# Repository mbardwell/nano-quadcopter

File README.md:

# Nano Quadcopter Project

## Overview

Welcome to the Nano Quadcopter project! This repository contains all the necessary files and instructions to build and program your own nano quadcopter.

The repository is in such a state that it would be better used as source code than an instruction manual.

This project is heavily inspired by Carbon Aeronautic's drone series [YT](https://www.youtube.com/@carbonaeronautics).

## Features

- Compact and lightweight design
- Easy to assemble
- Customizable firmware
- Open-source hardware and software

## Getting Started

### Prerequisites

- KiCad installed
- Arduino installed
- Electronics and soldering equipment

## License

This project is licensed under a standard MIT License.

## Contact

For any questions or feedback, please open an issue or contact us at [github.com.casually782@passinbox.com](mailto:github.com.casually782@passinbox.com).

Happy flying!

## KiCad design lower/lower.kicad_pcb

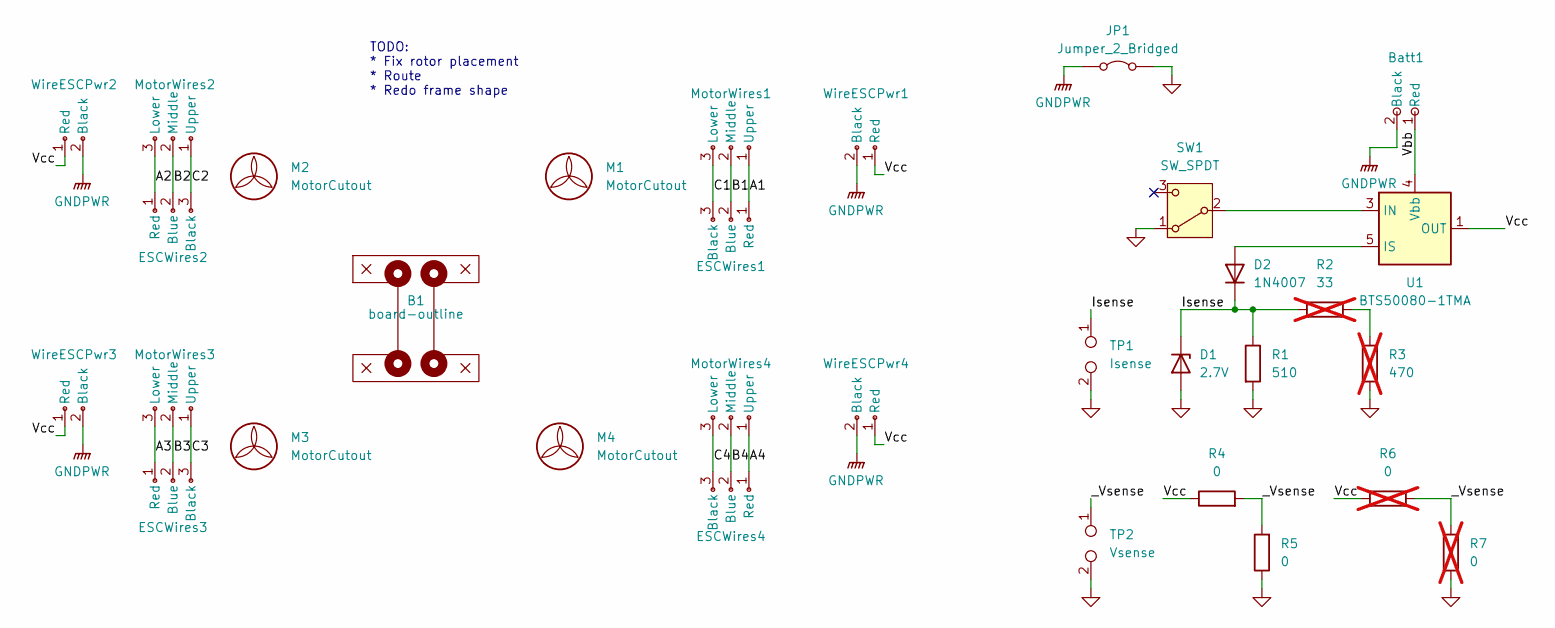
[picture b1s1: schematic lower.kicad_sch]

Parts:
B1: board-outline; board-outline-test
Batt1: WireBatt
D1: 2.7V; D_T-1_P5.08mm_Horizontal
D2: 1N4007; D_DO-41_SOD81_P10.16mm_Horizontal
ESCWires1, ESCWires2, ESCWires3, ESCWires4: WireESC
H1, H2, H3, H4: MountingHole; MountingHole_3.2mm_M3_ISO14580
JP1: Jumper_2_Bridged; SolderJumperLarge
M1, M2, M3, M4: MotorCutout; MotorEdges
MotorWires1, MotorWires2, MotorWires3, MotorWires4: WireMotor
R1: 510; R_0201_0603Metric_Pad0.64x0.40mm_HandSolder
R2: 33; R_Axial_DIN0207_L6.3mm_D2.5mm_P7.62mm_Horizontal; not fitted
R3: 470; R_Axial_DIN0207_L6.3mm_D2.5mm_P7.62mm_Horizontal; not fitted
R4, R5: 0; R_1206_3216Metric_Pad1.30x1.75mm_HandSolder
R6, R7: 0; R_Axial_DIN0207_L6.3mm_D2.5mm_P7.62mm_Horizontal; not fitted
SW1: SW_SPDT; SW_Slide_SPDT_Angled_CK_OS102011MA1Q
TP1: Isense; TestPoint_2Pads_Pitch2.54mm_Drill0.8mm
TP2: Vsense; TestPoint_2Pads_Pitch2.54mm_Drill0.8mm
U1: BTS50080-1TMA; TO-263-7_TabPin4
WireESCPwr1, WireESCPwr2, WireESCPwr3, WireESCPwr4: WireESCPwr

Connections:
/A1: ESCWires1.1 (Red), MotorWires1.1 (Upper)
/A2: ESCWires2.1 (Red), MotorWires2.3 (Lower)
/A3: ESCWires3.1 (Red), MotorWires3.3 (Lower)
/A4: ESCWires4.1 (Red), MotorWires4.1 (Upper)
/B1: ESCWires1.2 (Blue), MotorWires1.2 (Middle)
/B2: ESCWires2.2 (Blue), MotorWires2.2 (Middle)
/B3: ESCWires3.2 (Blue), MotorWires3.2 (Middle)
/B4: ESCWires4.2 (Blue), MotorWires4.2 (Middle)
/C1: ESCWires1.3 (Black), MotorWires1.3 (Lower)
/C2: ESCWires2.3 (Black), MotorWires2.1 (Upper)
/C3: ESCWires3.3 (Black), MotorWires3.1 (Upper)
/C4: ESCWires4.3 (Black), MotorWires4.3 (Lower)
/Isense: D1.1 (K), D2.1 (K), R1.1, R2.1, TP1.1
/Vbb: Batt1.1 (Red), U1.4 (Vbb)
/Vcc: R4.1, R6.1, U1.1 (OUT), U1.2 (OUT), U1.6 (OUT), U1.7 (OUT), WireESCPwr1.1 (Red), WireESCPwr2.1 (Red), WireESCPwr3.1 (Red), WireESCPwr4.1 (Red)
/_Vsense: R4.2, R5.2, R6.2, R7.1, TP2.1
GND: D1.2 (A), JP1.2 (B), R1.2, R3.2, R5.1, R7.2, SW1.1 (A), TP1.2, TP2.2
GNDPWR: Batt1.2 (Black), JP1.1 (A), WireESCPwr1.2 (Black), WireESCPwr2.2 (Black), WireESCPwr3.2 (Black), WireESCPwr4.2 (Black)
unnamed: D2.2 (A), U1.5 (IS)
unnamed: R2.2, R3.1
unnamed: SW1.2 (B), U1.3 (IN)

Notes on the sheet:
TODO: * Fix rotor placement * Route * Redo frame shape

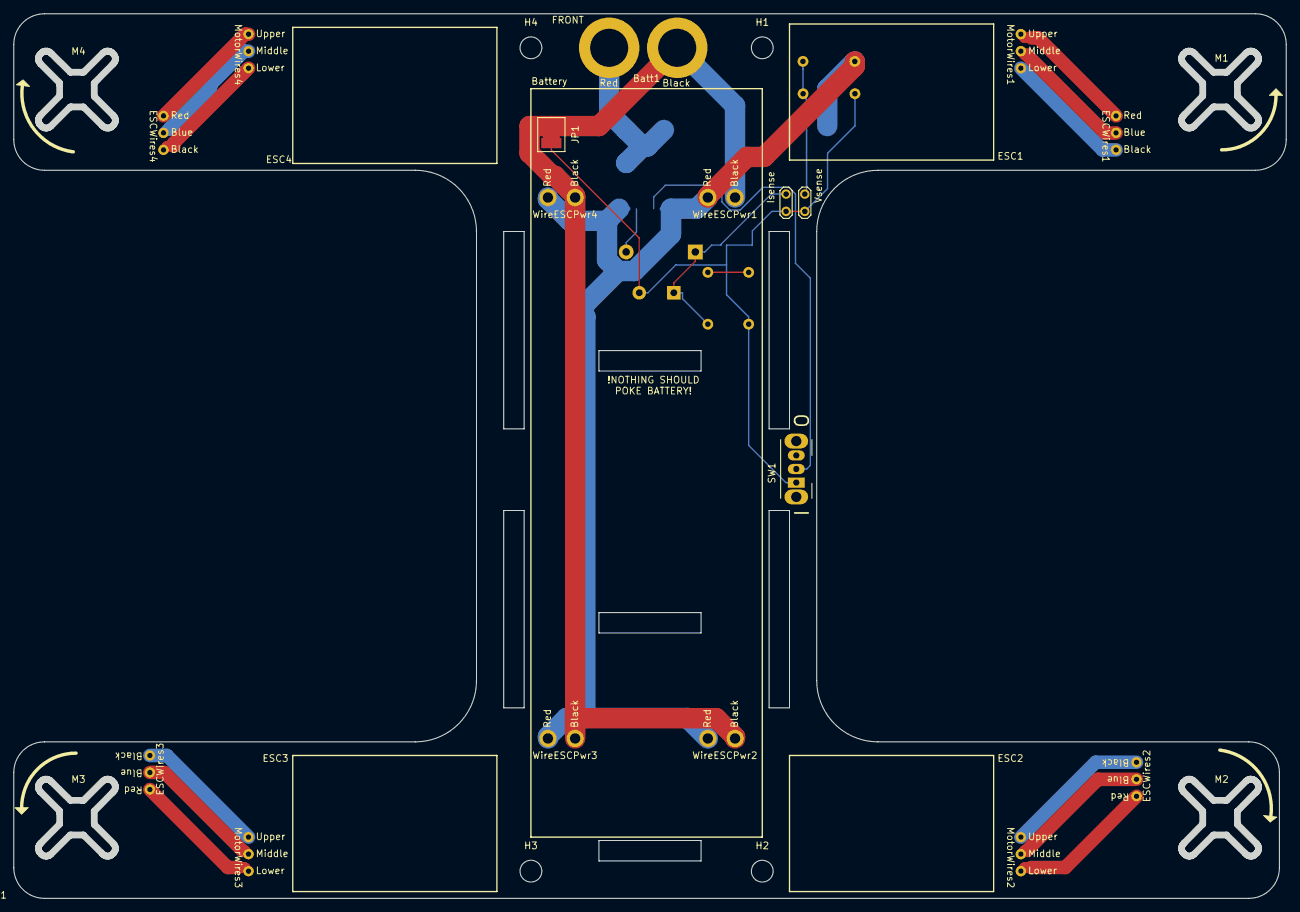
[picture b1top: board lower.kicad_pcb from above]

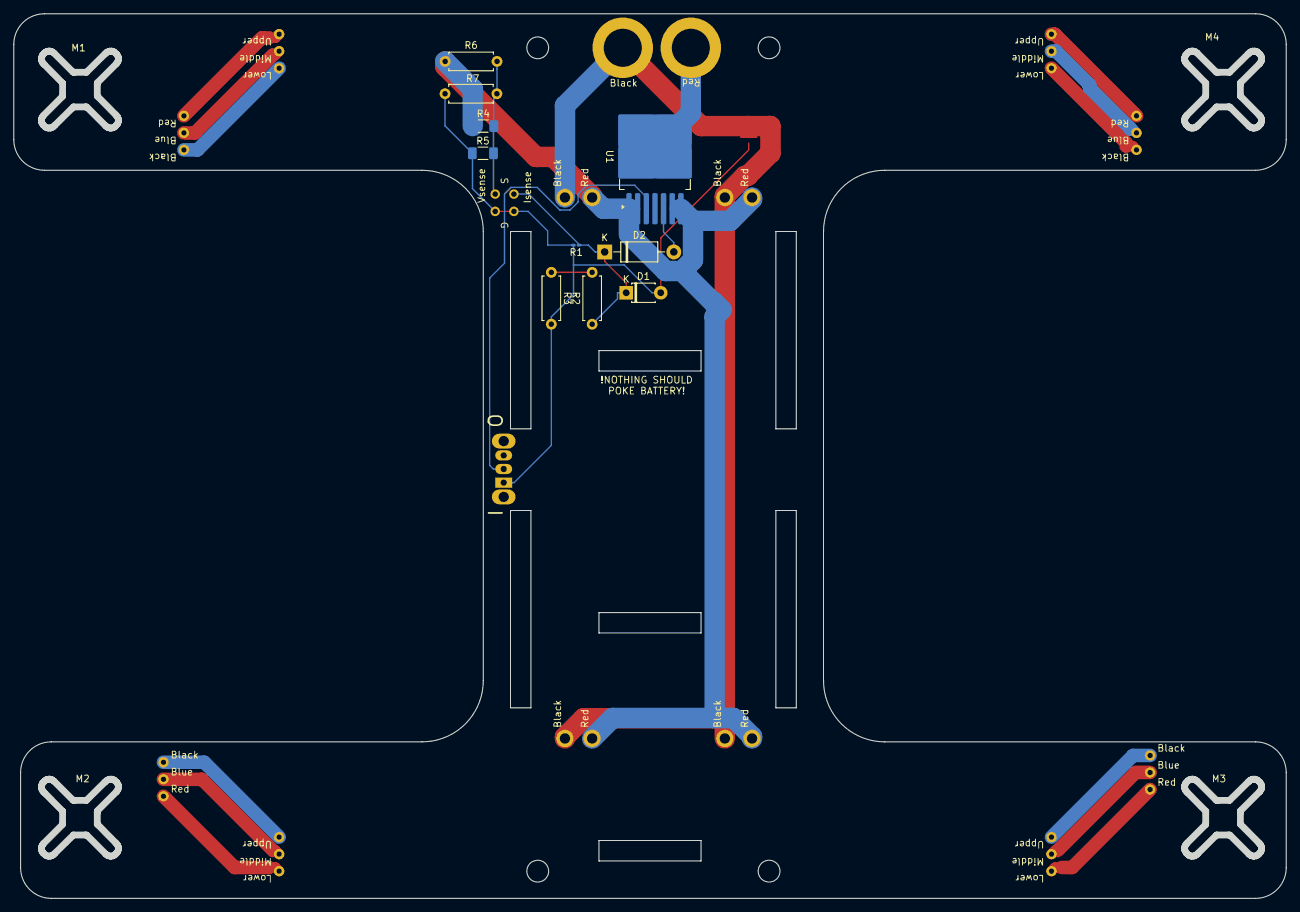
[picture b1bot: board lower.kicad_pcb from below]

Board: 2 copper layers, 187.0 x 130.0 mm, 36 parts (10 on the bottom side), 21 nets.

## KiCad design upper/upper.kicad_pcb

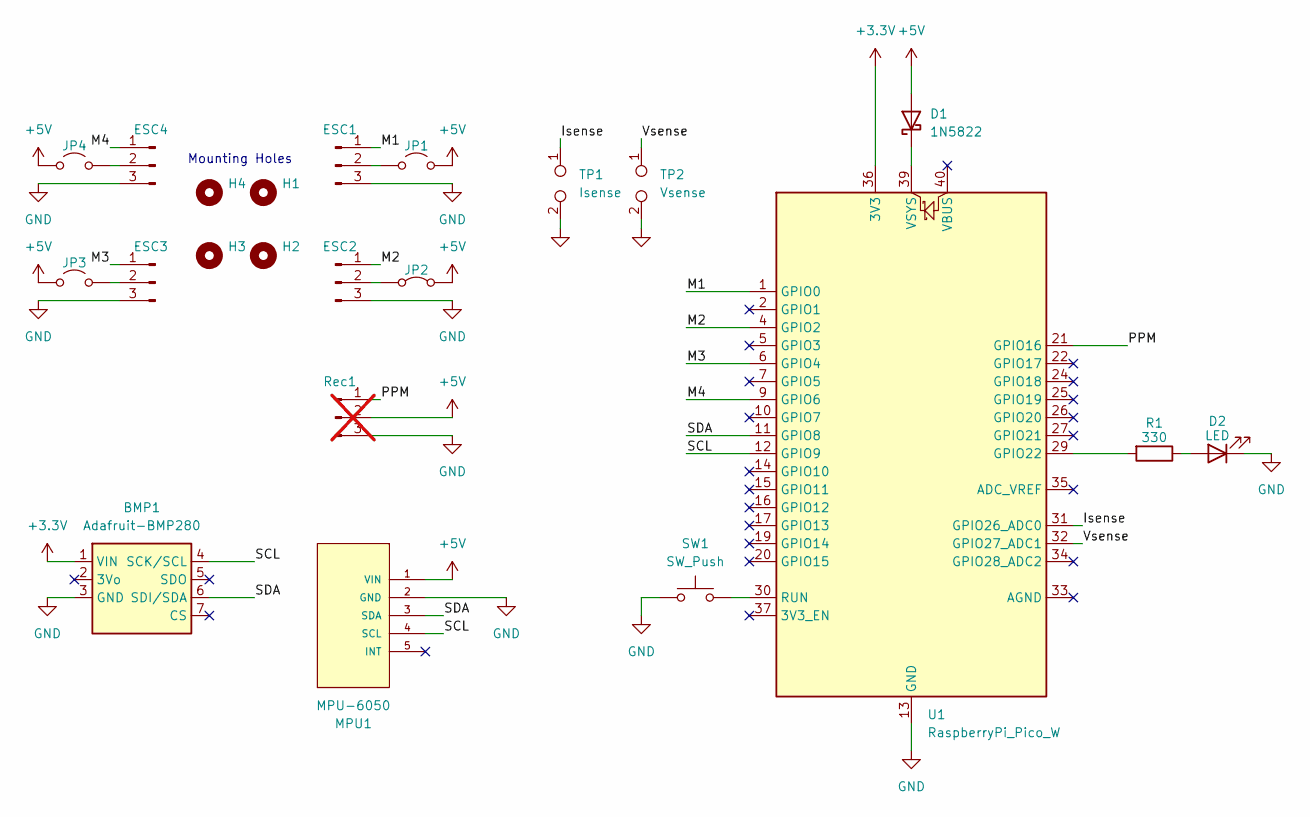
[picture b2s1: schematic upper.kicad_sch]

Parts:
BMP1: Adafruit-BMP280; adafruit-bmp280
D1: 1N5822; D_SMC_Handsoldering
D2: LED; LED_1206_3216Metric_Pad1.42x1.75mm_HandSolder
ESC1, ESC2, ESC3, ESC4: PinHeader_1x03_P2.54mm_Vertical
H1, H2, H3, H4: MountingHole; MountingHole_3.2mm_M3_ISO14580
JP1, JP3, JP4: Jumper_2_Open; SolderJumper-2_P1.3mm_Open_RoundedPad1.0x1.5mm
JP2: Jumper_2_Bridged; SolderJumper-2_P1.3mm_Bridged_RoundedPad1.0x1.5mm
MPU1: MPU-6050; SEN0142
R1: 330; R_0805_2012Metric_Pad1.20x1.40mm_HandSolder
Rec1: PinHeader_1x03_P2.54mm_Vertical; not fitted
SW1: SW_Push; SW_Push_1P1T_NO_6x6mm_H9.5mm
TP1: Isense; TestPoint_2Pads_Pitch2.54mm_Drill0.8mm
TP2: Vsense; TestPoint_2Pads_Pitch2.54mm_Drill0.8mm
U1: RaspberryPi_Pico_W; RaspberryPi_Pico_Common

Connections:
+3.3V: BMP1.1 (VIN), U1.36 (3V3)
+5V: D1.2 (A), JP1.2 (B), JP2.2 (B), JP3.1 (A), JP4.1 (A), MPU1.1 (VIN), Rec1.2
/Isense: TP1.1, U1.31 (GPIO26_ADC0)
/M1: ESC1.1, U1.1 (GPIO0)
/M2: ESC2.1, U1.4 (GPIO2)
/M3: ESC3.1, U1.6 (GPIO4)
/M4: ESC4.1, U1.9 (GPIO6)
/PPM: Rec1.1, U1.21 (GPIO16)
/SCL: BMP1.4 (SCK/SCL), MPU1.4 (SCL), U1.12 (GPIO9)
/SDA: BMP1.6 (SDI/SDA), MPU1.3 (SDA), U1.11 (GPIO8)
/Vsense: TP2.1, U1.32 (GPIO27_ADC1)
GND: BMP1.3 (GND), D2.1 (K), ESC1.3, ESC2.3, ESC3.3, ESC4.3, MPU1.2 (GND), Rec1.3, SW1.1, TP1.2, TP2.2, U1.3 (GND), U1.8 (GND), U1.13 (GND), U1.18 (GND), U1.23 (GND), U1.28 (GND), U1.38 (GND)
unnamed: D1.1 (K), U1.39 (VSYS)
unnamed: D2.2 (A), R1.1
unnamed: ESC1.2, JP1.1 (A)
unnamed: ESC2.2, JP2.1 (A)
unnamed: ESC3.2, JP3.2 (B)
unnamed: ESC4.2, JP4.2 (B)
unnamed: R1.2, U1.29 (GPIO22)
unnamed: SW1.2, U1.30 (RUN)

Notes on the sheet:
Mounting Holes

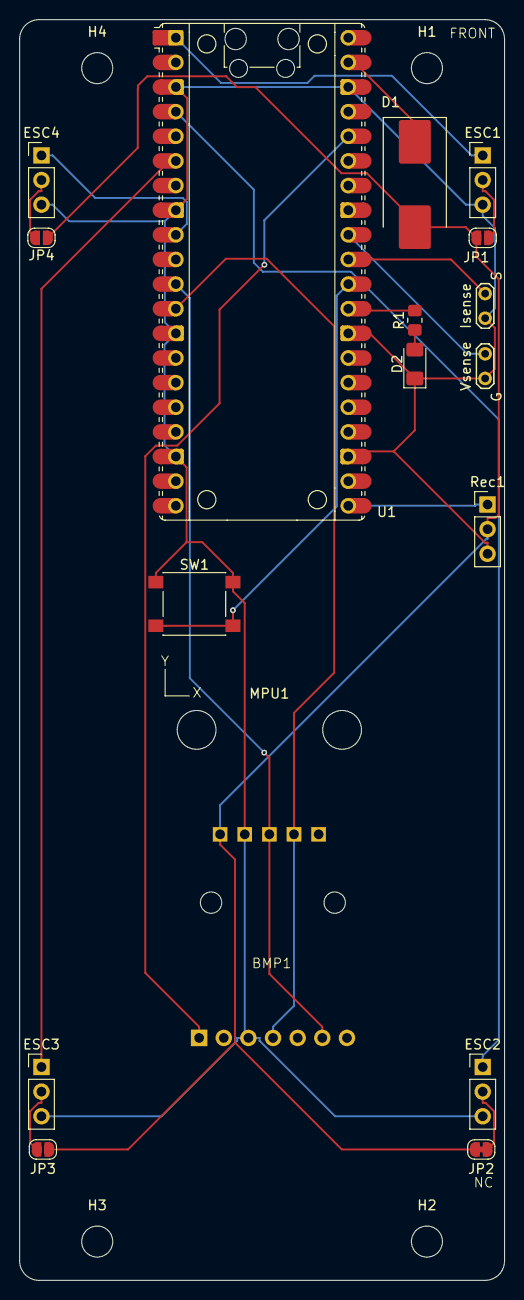
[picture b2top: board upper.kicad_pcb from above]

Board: 2 copper layers, 50.0 x 130.0 mm, 22 parts (0 on the bottom side), 20 nets.

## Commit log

2024-09-11 Init
2024-09-11 Split into upper and lower projects
2024-09-11 Quick lower PCB for cost estimation
2024-09-11 Init .gitignore
2024-09-16 Lower v0.1.0. Pre-routing
2024-09-16 Lower v0.1.1. Pre-routing
2024-09-17 Lower v0.1.2. Pre-routing
2024-09-17 v0.1.2. Routed
2024-09-17 Upper v0.0.1. Pre-routed
2024-09-17 Remove incorrectly tracked files
2024-09-17 Upper v0.1.0. Pre-routed
2024-09-18 Upper/Lower: v0.2.0. Pre-routed
2024-09-18 Upper/Lower: v0.2.0. Routed
2024-09-18 Lower: v0.2.1. Routed
2024-09-18 Upper: Small file changes
2024-09-18 Lower: Small file changes
2024-09-30 Firmware: Init BMP
2024-09-30 Firmware: Update varnames
2024-09-30 Firmware: Init MPU
2024-09-30 Firmware: Init power sensing
2024-09-30 Upper/Lower: Add notes
2024-09-30 Firmware: Add in motors
2024-09-30 Upper/Lower: Add post-assembly fixup comments
2024-09-30 Init firmware
2024-09-30 Firmware: Add control webserver
2024-10-14 Firmware: Add emergency state reset button
2024-10-14 Firmware: Add I/V info to webserver
2024-10-14 Firmware: Only turn off motors during emergency
2024-10-14 Firmware: Add IMU calibration step
2024-10-16 Firmware: Roughly cut in PID control
2024-10-17 Firmware: Update fnames to IMU/Pressure
2024-10-17 Firmware: Minor cosmetic
2024-10-17 Firmware: Better Roll/Pitch/Yaw data handling
2024-10-17 Firmware: Decompose motor calculations
2024-10-21 Firmware: Reduce emergency variable scope
2024-10-21 Firmware: Fixed IMU calibration
2024-10-22 Firmware: Added motor off print
2024-10-22 Firmware: Add motor signal handling
2024-10-22 Firmware: Try to fix motor value POST. Still issues, but getting there
2024-10-22 Firmware: Motor values pseudo-updating each loop
2024-10-23 Firmware: Working proportional control
2024-10-31 Firmware: Web interface works. Facelift
2024-10-31 Firmware: Serve running page immediately on exit from emergency
2024-11-02 Add README
2024-11-02 Firmware: Quadcopter responds to input throttle changes
2024-11-02 Firmware: Minor doc fixups
2024-11-02 Lower: Identify CW/CCW propellor in schematics
    From the top down:
    * CCW is 3025
    * CW is 3025R
2024-11-02 Firmware: Add altitude calculations
2024-11-02 Firmware: Web interface displays I/V/Alt/IMU Cal/Alt Cal
2024-11-02 Firmware: Make web interface slightly more readable
2024-11-02 Firmware: Change directory name to firmware/
2024-11-02 Firmware: Add angular rate emergency cutoff
2024-11-02 Firmware: Increase angular rate cutoff to 150. Ignore yaw
2024-11-04 Firmware: Leave headroom for R/P/Y at max throttle
2024-11-04 Firmware: Init download data button
2024-11-04 Firmware: Rename Telemetry to Web Data
    To make room for another telemetry type
2024-11-05 Firmware: Log to circular buffer
2024-11-06 Firmware: Download button gives 2000 pre-emergency samples
2024-11-07 Firmware: Add filedoc
2024-11-07 Firmware: Add roll, pitch, yaw docstring
2024-11-07 Upper: Add to v1 issues list
2024-11-10 Ignore pyenvs
2024-11-10 Initialize Python data interpreter
2024-11-10 Scripting: Send reset. Plot motor values
2024-11-11 Firmware: Update motor signal calculations. Report raw IMU output
2024-11-11 Firmware: Add roll/pitch/yaw correction on/off user input
2024-11-11 Firmware: Increase yaw P-coeff to 2.0
2024-11-11 Scripting: Decrease GET /reset timeout
2024-11-11 Firmware: Remove motor compensation. Reduce pitch and yaw P-coeff
2024-11-11 Firmware: Expose roll/pitch/yaw P-coeff to user
2024-11-11 Firmware: Enable Integral and Derivative control
2024-11-11 Firmware: Pulse motor low at start to ensure blades are already spinning
2024-11-11 Firmware: User can change all PID coeffs
2024-11-16 Firmware: Move code to flight-controller dir
2024-11-16 FC: Update docs
2024-11-18 ESC Settings: Control with up/down arrow keys
2024-11-18 ESC Settings: Add docs
2024-11-18 FC: Remove magic terms from PID equation
    KISS
2024-11-18 FC: Reset PID controller memory when motors off
2024-11-18 FC: Reduce integral coeffs
2024-11-19 FC: Remove angular rate emergency trigger. Increase emergency timeout to 1 minute
2024-11-25 FC: Move IMU logic to setup function. Tighten LPF from 10->5Hz. Use recommend clock source
2024-11-25 FC: Minor readability change
2024-12-02 FC: Add missing pitch proportional field on webserver
2024-12-02 FC: Fix webserver sigdigs
2024-12-02 FC: Cap I & D terms. Update on regular 1ms intervals
